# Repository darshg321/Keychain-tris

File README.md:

# Keychain-tris

i made this project as a speedrun before the end of fallout for funsies. it is (hopefully) tetris on a keychain! how it will work is that you will be able to play tetris on the oled screen by moving the pcb around, and the imu will detect the movements. so for example, moving right will move the pieces right, and moving it down will drop it. whats great about this control method is that theres 6 axis of motion so theres plenty to work with.

the pcb has:
- an esp32c3
- a type c port for power/programming
- a lipo board
- 3v3 ldo
- and of course the imu which is an mpu 6050

## Poster (Zine)

## PCB Render

## PCB

## Schematic

## Assembly:
- solder on components according to pcb layout
- plug in to usb and upload firmware
- play tetris!

## BOM

|Reference                 |Value                      |Footprint                                                 |Datasheet                                                                                                 |Qty|DNP|Exclude from BOM|Exclude from Board|
|--------------------------|---------------------------|----------------------------------------------------------|----------------------------------------------------------------------------------------------------------|---|---|----------------|------------------|
|AE1                       |2450AT18A100E              |easyeda2kicad:ANT-SMD_L3.2-W1.6                           |https://lcsc.com/product-detail/RF-Antenna_JOHANSON_2450AT18A100E_2450AT18A100E_C89334.html               |1  |   |                |                  |
|C1,C2,C5,C8,C9,C10,C15,C17|100nF                      |Capacitor_SMD:C_0805_2012Metric                           |~                                                                                                         |8  |   |                |                  |
|C3,C4                     |10uF                       |Capacitor_SMD:C_0805_2012Metric                           |~                                                                                                         |2  |   |                |                  |
|C6,C7,C13,C16             |1uF                        |Capacitor_SMD:C_0805_2012Metric                           |~                                                                                                         |4  |   |                |                  |
|C11,C12                   |18pF                       |Capacitor_SMD:C_0805_2012Metric                           |~                                                                                                         |2  |   |                |                  |
|C14                       |1pF                        |Capacitor_SMD:C_0805_2012Metric                           |~                                                                                                         |1  |   |                |                  |
|C18                       |2.2uF                      |Capacitor_SMD:C_0805_2012Metric                           |~                                                                                                         |1  |   |                |                  |
|J1                        |Conn_01x02                 |Connector_PinSocket_2.54mm:PinSocket_1x02_P2.54mm_Vertical|~                                                                                                         |1  |   |                |                  |
|J2                        |USB_C_Receptacle_USB2.0_16P|Connector_USB:USB_C_Receptacle_HRO_TYPE-C-31-M-12         |https://www.usb.org/sites/default/files/documents/usb_type-c.zip                                          |1  |   |                |                  |
|J3                        |Conn_01x04                 |Connector_PinHeader_2.54mm:PinHeader_1x04_P2.54mm_Vertical|~                                                                                                         |1  |   |                |                  |
|J4,J5                     |Conn_01x08                 |Connector_PinSocket_2.54mm:PinSocket_1x08_P2.54mm_Vertical|~                                                                                                         |2  |   |                |                  |
|L1                        |BLM18KG601SN1D             |easyeda2kicad:L0603                                       |https://lcsc.com/product-detail/Ferrite-Beads-And-Chips_muRata_BLM18KG601SN1D_600R-25-at100MHz_C85833.html|1  |   |                |                  |
|L2                        |SDCL1005C2N7STDF           |easyeda2kicad:L0402                                       |https://lcsc.com/product-detail/HF-Inductors_2-7nH-0-3nH_C27123.html                                      |1  |   |                |                  |
|L3                        |SDCL1608C3N9STDF           |easyeda2kicad:L0603                                       |https://lcsc.com/product-detail/HF-Inductors_3-9nH-0-3nH_C13818.html                                      |1  |   |                |                  |
|R1,R2                     |5.1K                       |Resistor_SMD:R_0805_2012Metric                            |~                                                                                                         |2  |   |                |                  |
|R3,R4,R5                  |10K                        |Resistor_SMD:R_0805_2012Metric                            |~                                                                                                         |3  |   |                |                  |
|R6                        |50                         |Resistor_SMD:R_0805_2012Metric                            |~                                                                                                         |1  |   |                |                  |
|SW1,SW2                   |TS24CA                     |easyeda2kicad:SW-SMD_2P-TS24CA                            |https://lcsc.com/product-detail/Tactile-Switches_SHOU-HAN-TS24CA_C393942.html                             |2  |   |                |                  |
|TP1                       |TestPoint                  |TestPoint:TestPoint_Pad_D1.0mm                            |~                                                                                                         |1  |   |                |                  |
|U1                        |ESP32-C3                   |Package_DFN_QFN:QFN-32-1EP_5x5mm_P0.5mm_EP3.7x3.7mm       |https://www.espressif.com/sites/default/files/documentation/esp32-c3_datasheet_en.pdf                     |1  |   |                |                  |
|U2                        |AMS1117-3.3                |Package_TO_SOT_SMD:SOT-223-3_TabPin2                      |http://www.advanced-monolithic.com/pdf/ds1117.pdf                                                         |1  |   |                |                  |
|U3                        |MPU-6050_C24112            |easyeda2kicad:QFN-24_L4.0-W4.0-P0.50-BL-EP2.7             |https://lcsc.com/product-detail/Sensors_InvenSense_MPU6050_MPU-6050_C24112.html                           |1  |   |                |                  |
|X1                        |3225 40M 12PF 10PPM        |easyeda2kicad:CRYSTAL-SMD_4P-L3.2-W2.5-BL                 |https://www.lcsc.com/datasheet/C5380316.pdf                                                               |1  |   |                |                  |

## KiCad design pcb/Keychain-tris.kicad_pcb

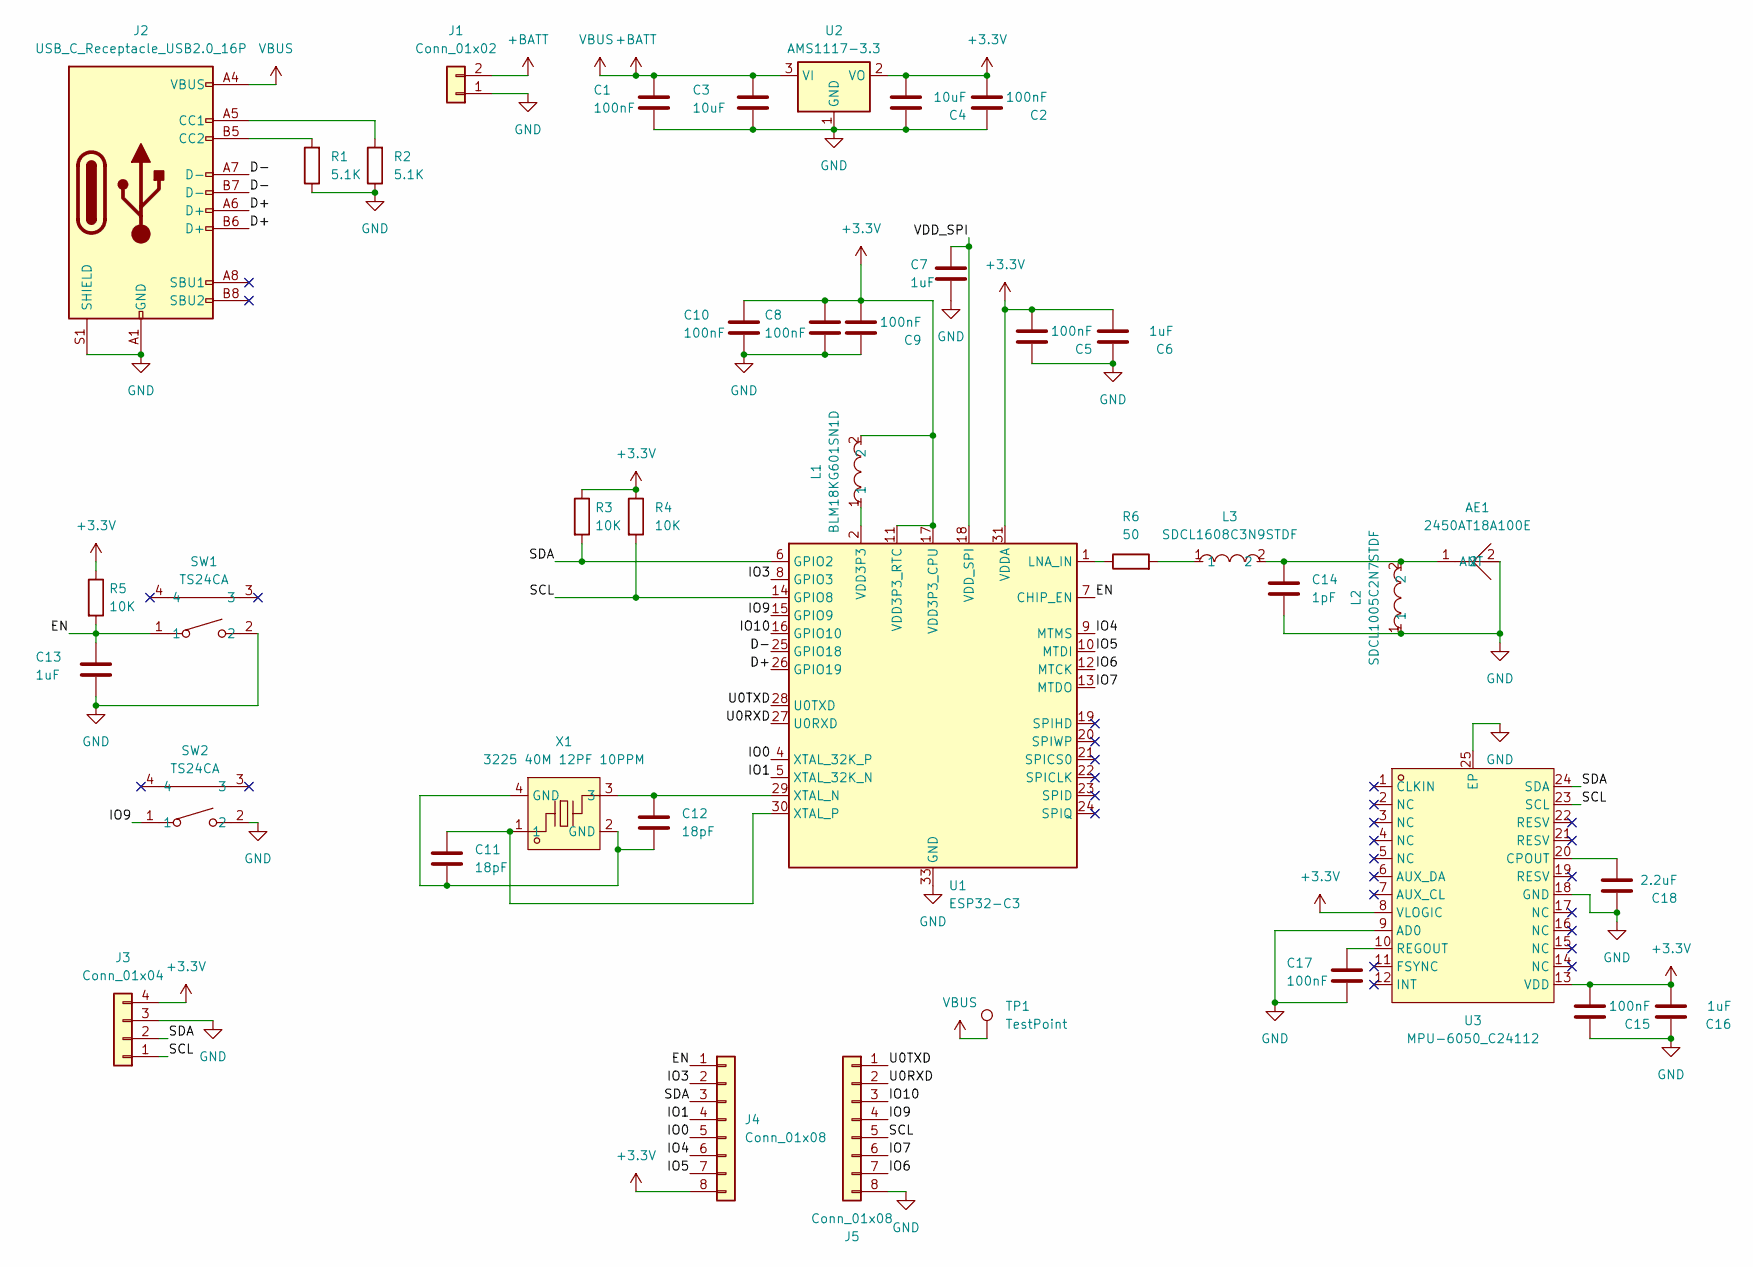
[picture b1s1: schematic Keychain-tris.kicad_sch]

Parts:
AE1: 2450AT18A100E; ANT-SMD_L3.2-W1.6; MPN 2450AT18A100E; LCSC Part C89334
C1, C2, C5, C8, C9, C10, C15, C17: 100nF; C_0805_2012Metric
C3, C4: 10uF; C_0805_2012Metric
C6, C7, C13, C16: 1uF; C_0805_2012Metric
C11, C12: 18pF; C_0805_2012Metric
C14: 1pF; C_0805_2012Metric
C18: 2.2uF; C_0805_2012Metric
J1: Conn_01x02; PinSocket_1x02_P2.54mm_Vertical
J2: USB_C_Receptacle_USB2.0_16P; USB_C_Receptacle_HRO_TYPE-C-31-M-12
J3: Conn_01x04; PinHeader_1x04_P2.54mm_Vertical
J4, J5: Conn_01x08; PinSocket_1x08_P2.54mm_Vertical
L1: BLM18KG601SN1D; L0603; MPN BLM18KG601SN1D; LCSC Part C85833
L2: SDCL1005C2N7STDF; L0402; MPN SDCL1005C2N7STDF; LCSC Part C27123
L3: SDCL1608C3N9STDF; L0603; MPN SDCL1608C3N9STDF; LCSC Part C13818
R1, R2: 5.1K; R_0805_2012Metric
R3, R4, R5: 10K; R_0805_2012Metric
R6: 50; R_0805_2012Metric
SW1, SW2: TS24CA; SW-SMD_2P-TS24CA; MPN TS24CA; LCSC Part C393942
TP1: TestPoint; TestPoint_Pad_D1.0mm
U1: ESP32-C3; QFN-32-1EP_5x5mm_P0.5mm_EP3.7x3.7mm
U2: AMS1117-3.3; SOT-223-3_TabPin2
U3: MPU-6050_C24112; QFN-24_L4.0-W4.0-P0.50-BL-EP2.7; MPN MPU-6050; LCSC Part C24112
X1: 3225 40M 12PF 10PPM; CRYSTAL-SMD_4P-L3.2-W2.5-BL; MPN 3225 40M 12PF 10PPM; LCSC Part C5380316

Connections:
+3.3V: C2.2, C4.2, C5.2, C6.2, C8.1, C9.2, C10.1, C15.2, C16.2, J3.4, J4.8, L1.2, R3.1, R4.1, R5.1, U1.11 (VDD3P3_RTC), U1.17 (VDD3P3_CPU), U1.31 (VDDA), U1.32 (VDDA), U2.2 (VO), U3.8 (VLOGIC), U3.13 (VDD)
+BATT: C1.1, C3.1, J1.2, J2.A4 (VBUS), J2.A9 (VBUS), J2.B4 (VBUS), J2.B9 (VBUS), TP1.1, U2.3 (VI)
/D+: J2.A6 (D+), J2.B6 (D+), U1.26 (GPIO19)
/D-: J2.A7 (D-), J2.B7 (D-), U1.25 (GPIO18)
/EN: C13.1, J4.1, R5.2, SW1.1, U1.7 (CHIP_EN)
/IO0: J4.5, U1.4 (XTAL_32K_P)
/IO1: J4.4, U1.5 (XTAL_32K_N)
/IO3: J4.2, U1.8 (GPIO3)
/IO4: J4.6, U1.9 (MTMS)
/IO5: J4.7, U1.10 (MTDI)
/IO6: J5.7, U1.12 (MTCK)
/IO7: J5.6, U1.13 (MTDO)
/IO9: J5.4, SW2.1, U1.15 (GPIO9)
/IO10: J5.3, U1.16 (GPIO10)
/SCL: J3.1, J5.5, R4.2, U1.14 (GPIO8), U3.23 (SCL)
/SDA: J3.2, J4.3, R3.2, U1.6 (GPIO2), U3.24 (SDA)
/U0RXD: J5.2, U1.27 (U0RXD)
/U0TXD: J5.1, U1.28 (U0TXD)
/VDD_SPI: C7.1, U1.18 (VDD_SPI)
GND: AE1.2, C1.2, C2.1, C3.2, C4.1, C5.1, C6.1, C7.2, C8.2, C9.1, C10.2, C13.2, C14.2, C15.1, C16.1, C17.2, C18.1, J1.1, J2.A1 (GND), J2.A12 (GND), J2.B1 (GND), J2.B12 (GND), J2.S1 (SHIELD), J3.3, J5.8, L2.1, R1.1, R2.1, SW1.2, SW2.2, U1.33 (GND), U2.1 (GND), U3.9 (AD0), U3.18 (GND), U3.25 (EP)
unnamed: AE1.1 (ANT), C14.1, L2.2, L3.2
unnamed: C11.1, C12.1, X1.2 (GND), X1.4 (GND)
unnamed: J2.A5 (CC1), R2.2
unnamed: J2.B5 (CC2), R1.2
unnamed: L1.1, U1.2 (VDD3P3), U1.3 (VDD3P3)
unnamed: L3.1, R6.2
unnamed: R6.1, U1.1 (LNA_IN)
unnamed: C12.2, U1.29 (XTAL_N), X1.3
unnamed: C11.2, U1.30 (XTAL_P), X1.1
unnamed: C18.2, U3.20 (CPOUT)
unnamed: C17.1, U3.10 (REGOUT)

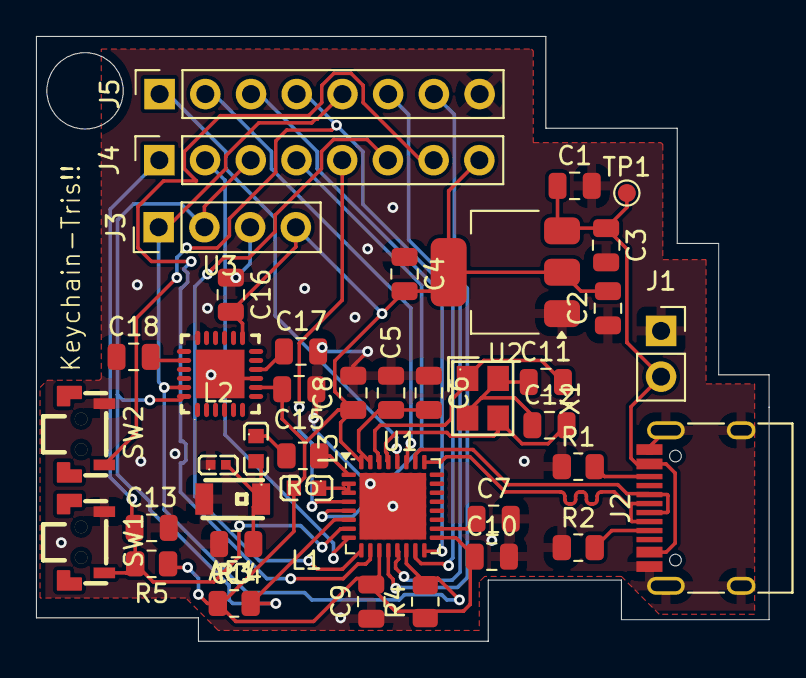
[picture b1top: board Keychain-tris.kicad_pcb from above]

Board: 2 copper layers, 40.7 x 33.6 mm, 40 parts (0 on the bottom side), 31 nets.

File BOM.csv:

"Reference","Value","Footprint","Datasheet","Qty","DNP","Exclude from BOM","Exclude from Board"
"AE1","2450AT18A100E","easyeda2kicad:ANT-SMD_L3.2-W1.6","https://lcsc.com/product-detail/RF-Antenna_JOHANSON_2450AT18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","1","","",""
"C1,C2,C5,C8,C9,C10,C15,C17","100nF","Capacitor_SMD:C_0805_2012Metric","~","8","","",""
"C3,C4","10uF","Capacitor_SMD:C_0805_2012Metric","~","2","","",""
"C6,C7,C13,C16","1uF","Capacitor_SMD:C_0805_2012Metric","~","4","","",""
"C11,C12","18pF","Capacitor_SMD:C_0805_2012Metric","~","2","","",""
"C14","1pF","Capacitor_SMD:C_0805_2012Metric","~","1","","",""
"C18","2.2uF","Capacitor_SMD:C_0805_2012Metric","~","1","","",""
"J1","Conn_01x02","Connector_PinSocket_2.54mm:PinSocket_1x02_P2.54mm_Vertical","~","1","","",""
"J2","USB_C_Receptacle_USB2.0_16P","Connector_USB:USB_C_Receptacle_HRO_TYPE-C-31-M-12","https://www.usb.org/sites/default/files/documents/usb_type-c.zip","1","","",""
"J3","Conn_01x04","Connector_PinHeader_2.54mm:PinHeader_1x04_P2.54mm_Vertical","~","1","","",""
"J4,J5","Conn_01x08","Connector_PinSocket_2.54mm:PinSocket_1x08_P2.54mm_Vertical","~","2","","",""
"L1","BLM18KG601SN1D","easyeda2kicad:L0603","https://lcsc.com/product-detail/Ferrite-Beads-And-Chips_muRa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","1","","",""
"L2","SDCL1005C2N7STDF","easyeda2kicad:L0402","https://lcsc.com/product-detail/HF-Inductors_2-7nH-0-3nH_C27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","1","","",""
"L3","SDCL1608C3N9STDF","easyeda2kicad:L0603","https://lcsc.com/product-detail/HF-Inductors_3-9nH-0-3nH_C13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","1","","",""
"R1,R2","5.1K","Resistor_SMD:R_0805_2012Metric","~","2","","",""
"R3,R4,R5","10K","Resistor_SMD:R_0805_2012Metric","~","3","","",""
"R6","50","Resistor_SMD:R_0805_2012Metric","~","1","","",""
"SW1,SW2","TS24CA","easyeda2kicad:SW-SMD_2P-TS24CA","https://lcsc.com/product-detail/Tactile-Switches_SHOU-HAN-TS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","2","","",""
"TP1","TestPoint","TestPoint:TestPoint_Pad_D1.0mm","~","1","","",""
"U1","ESP32-C3","Package_DFN_QFN:QFN-32-1EP_5x5mm_P0.5mm_EP3.7x3.7mm","https://www.espressif.com/sites/default/files/documentation/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","1","","",""
"U2","AMS1117-3.3","Package_TO_SOT_SMD:SOT-223-3_TabPin2","http://www.advanced-monolithic.com/pdf/ds1117.pdf","1","","",""
"U3","MPU-6050_C24112","easyeda2kicad:QFN-24_L4.0-W4.0-P0.50-BL-EP2.7","https://lcsc.com/product-detail/Sensors_InvenSense_MPU6050_M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","1","","",""
"X1","3225 40M 12PF 10PPM","easyeda2kicad:CRYSTAL-SMD_4P-L3.2-W2.5-BL","https://www.lcsc.com/datasheet/C5380316.pdf","1","","",""

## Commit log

2026-06-21 almost done
2026-06-21 things
2026-06-21 fixes
2026-06-21 oops
